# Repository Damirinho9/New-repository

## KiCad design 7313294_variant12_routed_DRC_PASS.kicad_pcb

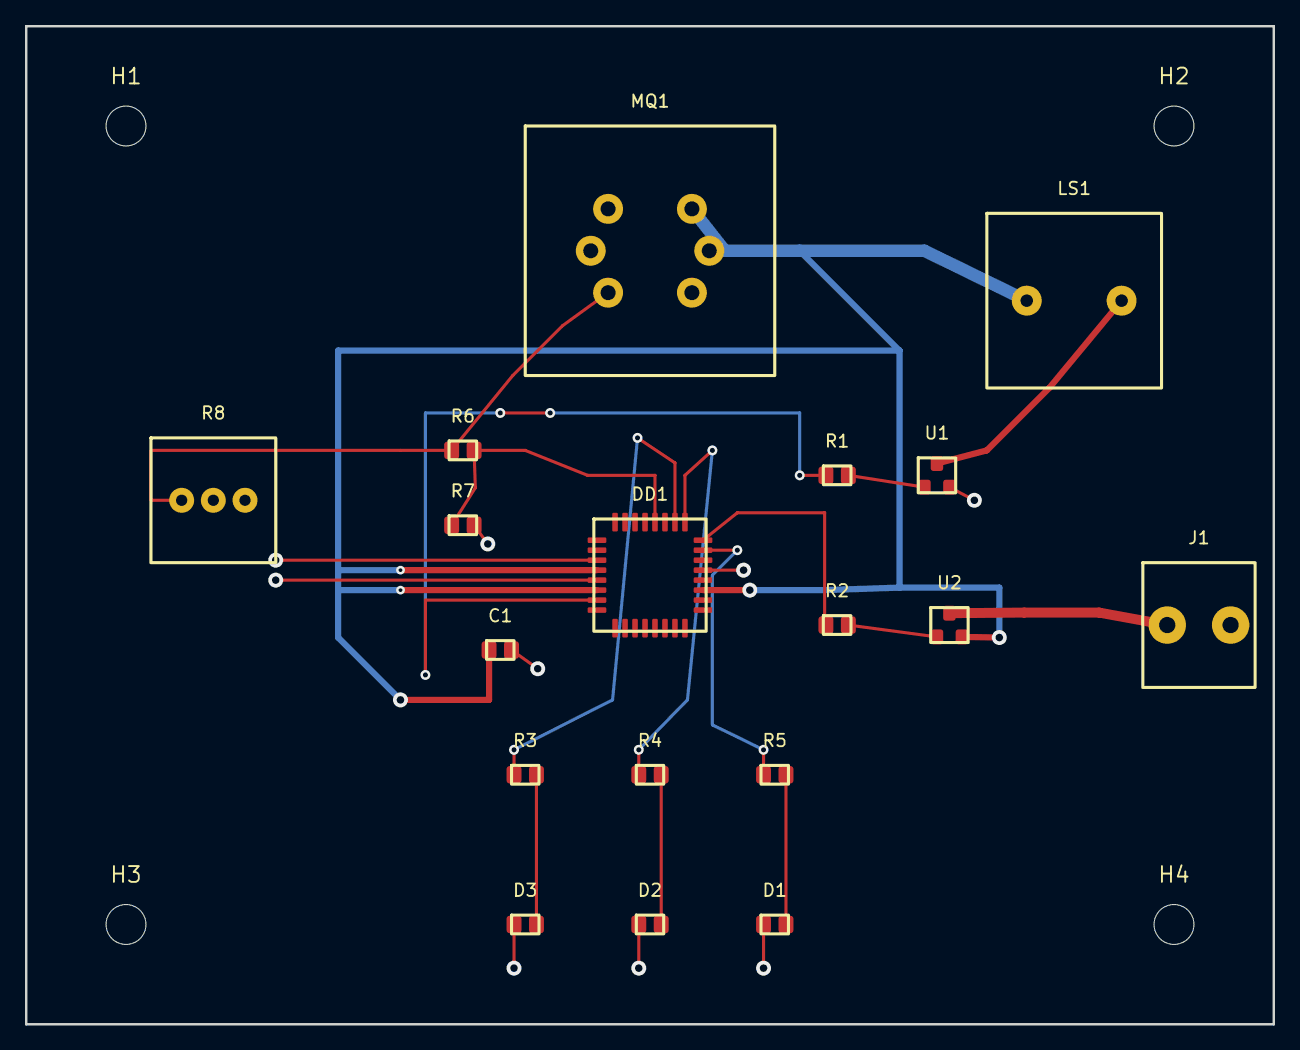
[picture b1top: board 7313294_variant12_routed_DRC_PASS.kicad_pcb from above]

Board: 2 copper layers, 100.0 x 80.0 mm, 22 parts (0 on the bottom side), 16 nets.

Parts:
C1: 100n; C1
D1: RED; D1
D2: GREEN; D2
D3: BLUE; D3
DD1: ATmega48A-AU; DD1
H1, H2, H3, H4: MountingHole_3.2mm
J1: TB 2P 5.08; J1
LS1: Active buzzer 5V; LS1
MQ1: MQ-4; MQ1
R1: 1k; R1
R2: 1k; R2
R3: 510; R3
R4: 510; R4
R5: 510; R5
R6: 4k7; R6
R7: 4k7; R7
R8: 20k 3296W; R8
U1: BC847; U1
U2: BC857; U2

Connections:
+5V: C1.1, DD1.4, DD1.6, DD1.19, LS1.1, MQ1.4, MQ1.5, U2.2
ADC_NODE: DD1.28, R6.2, R7.1
BUZZ_BASE: R1.2, U1.1
BUZZ_MCU: DD1.7, R1.1
BUZZ_SW: LS1.2, U1.3
GND: C1.2, D1.1, D2.1, D3.1, DD1.3, DD1.5, DD1.21, J1.2, MQ1.2, R7.2, R8.2, R8.3, U1.2
LED_B_A: D3.2, R3.2
LED_B_MCU: DD1.26, R3.1
LED_G_A: D2.2, R4.2
LED_G_MCU: DD1.25, R4.1
LED_R_A: D1.2, R5.2
LED_R_MCU: DD1.23, R5.1
OUT_BASE: R2.2, U2.1
OUT_MCU: DD1.24, R2.1
OUT_PLUS: J1.1, U2.3
SENSOR_OUT: MQ1.1, R6.1, R8.1

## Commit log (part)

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2025-09-01 Updated CSV file
